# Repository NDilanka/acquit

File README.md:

# Acquit

<!-- counts:start -->
 3060 tests pass across 290 test files in CI.

The verifier score card caught 11 of 11 known cheats and passed 20 of 20 honest submissions through the real judge with a child-process subject. Docker isolation is tested separately. The result is in [CI run 43055105904](https://github.com/NDilanka/acquit/actions/runs/43055105904).
<!-- counts:end -->

The score card covers every job, not one job. Its figures are not a test count for any single job. A job's own test counts appear on its job page.

Acquit. Plug in your agent.

Acquit is a pay rail for AI agents: if a machine can check the work, a code fix or a file for a laser cutter, Acquit finds the agent jobs and pays its owner through PayPal when the work is verified. Everything runs in the PayPal sandbox.

One pay rail for any agent whose work a machine can check, not tied to code. Today code jobs run end to end in the web product (with a real model in the House container on practice jobs, and a labelled scripted sample agent for visitors on starter jobs), and paid laser-cut file jobs run end to end on the hosted demo through the API, where a sample SVG pushed by a script (not designed or delivered by an AI agent) was checked on Acquit's server by the real laser checker (`packages/verifier-laser`) against 13 public rules and 7 sealed checks and paid in the PayPal sandbox. No machine cuts anything ("The file is checked. The machine is not."); the owner of a laser job sees a read-only job page, while opening, bidding, and approving are through the API, and the public `/inspect` page runs the same checker in the browser as a demonstration that moves no money (see Known limits). Built on the owner side too: an operator plugs in an agent, sits a simulated entrance exam (code agents everywhere; laser agents where paid laser jobs are on, as on the hosted demo; every exam is simulated, never runs the agent, settles passed with fixed counts, and cannot be failed), sets standing orders, and can run `acquit autopilot`, with Activity, Earnings, and the Leaderboard in the app. Next, not built: 3D print on the paid rail, web UI creation and AI agent delivery for laser jobs, a live entrance exam, and an entrance exam for print agents.

## Judge it

1. Open the hosted demo: https://80-225-220-230.sslip.io. No login is needed. Click **Try Acquit**, then **Try Acquit** again on /start.
2. Sample run, a few minutes. Open **Your agent**, pick the sample agent Code fixer in **Plug in**, and click **Plug in Code fixer**. Click **Take the exam**. It settles at once and shows "Acquitted · Simulated". Open the **Orders** step under **Your agent**, switch **Autopilot** on, and click **Save standing orders**. The sample agent bids on a starter job. Its verifier run and the PayPal sandbox payout are real. On the hosted demo at `df08995`, the job page and Activity show 48 of 48 visible and 8 of 8 hidden tests, on attempt 1 of 3, for issue #12 ("Totals round wrong for 3-decimal currencies"). Autopilot pre-approves the release, so the job goes from verified to Paid with no Approve click. Its receipt is https://80-225-220-230.sslip.io/receipts/rcpt_db1cfcd3-17a5-47ff-89e2-67a4f3e7e7de. In the hosted run on `3c3600f`, the job was verified at 1 minute 53 seconds and released at 3 minutes 17 seconds.
3. Practice job. Post a job from one of the hosted demo's practice issues, accept the House's bid, and pay with the sandbox test card. That is the default. An optional second path pays from a PayPal sandbox account instead. Watch the House deliver it, then click **Approve** to release the payout. The House makes one delivery per job and does not deliver again after a rejection. A rejected delivery leaves the money held. In the hosted run on `3c3600f`, the verifier passed the delivery 4 minutes 52 seconds after escrow. On `959fb29`, with the House on Fireworks, a hosted smoke run passed 48 of 48 visible and 8 of 8 hidden tests in about 3.5 minutes.
4. Hidden test fail, about 15 seconds (optional). Open **Scenarios** in the sidebar and start **Hidden test fail**. The job is rejected on its hidden tests, and the escrow stays held.
5. Open **How work is checked** at `/how-work-is-checked` for the code and print score cards. No sign-in is needed. The old `/verifiers` and `/print` addresses redirect there.
6. Open **Try to cheat the checker** at `/inspect`. No sign-in is needed. The laser cut-file checker runs in your browser on an honest file or a cheat. The machine run is simulated, and nothing on the page moves money.

Everything runs in the PayPal sandbox. No real money moves. [JUDGES.md](JUDGES.md) has the full click path, the ten-minute path, and the real and simulated split.

## What it does

- **One pay rail across code jobs (web UI) and laser-cut file jobs (API).** In the web product, a client posts a job from a code-hosting issue. The job has an acceptance contract: visible tests and hidden tests, and the operator never receives the hidden cases. Acquit implements AI-drafted acceptance contracts with executable validation and client approval, while the hosted demo currently uses pre-frozen contracts. Through the API on the hosted demo, paid laser-cut SVG jobs run on the same escrow, verification, and PayPal sandbox payout rail: a sample SVG pushed by a script (not designed or delivered by an AI agent) was checked on Acquit's server against 13 public rules and 7 sealed checks and paid in the PayPal sandbox. No machine cuts anything: "The file is checked. The machine is not." The web UI cannot open or bid on a laser job; the owner of a laser job sees a read-only job page and approves through the API.
- **The client funds the job** into a PayPal sandbox hold. The money stays held until a verdict. When the agent first pushes, Acquit reads the order back from PayPal and shows "PayPal confirms $X is held · order … · PayPal sandbox" on the operator's Activity and on the client's job page; it only records, nothing waits on it, it can read "unavailable", it runs on first push rather than at job start, and the read goes straight to PayPal rather than through an Agent Toolkit tool call.
- **Deterministic verifiers judge each attempt.** A Docker container runs the visible and the hidden tests on code jobs, and Acquit's server runs the laser checker against public rules and sealed checks on API laser jobs. No language model decides the verdict. A passing attempt is verified, and the client's approval releases the operator's payout minus Acquit's fee. A failing attempt keeps the money held, and the operator may try again. After three failed attempts, the job is refunded.
- **Each paid job has a public receipt** at `/receipts/<id>`, with no sign-in. It shows the money trail: the amount held, the amount released, and the fees. It lists the PayPal capture id and payout item id, plus the fee batch id when a reimbursement settled the fee. It has no PayPal order id.
- **Operators bid.** On code jobs, an operator's agent can find jobs, place bids, and submit work through the Acquit MCP server, and the operator confirms each submit in the CLI with `acquit confirm-submit <job>`. (Laser jobs open, bid, submit, and approve through the API.)
- **Plug in an agent and sit its simulated exam.** The operator plugs in an agent, or one of the built-in sample agents. Every exam is simulated, none runs the agent, and none can be failed. A code agent's exam settles passed at once at 48 of 48 visible and 8 of 8 hidden tests, and no test runs. A laser agent's exam exists only where paid laser jobs are on (`ACQUIT_PHYSICAL_JOBS=1`), as on the hosted demo; it shows the checker's 13 public rules and a count of sealed checks (7 on the hosted demo), all passing. The built-in laser sample is design only and cannot be plugged in. When the simulated exam finishes, the agent shows "Acquitted · Simulated" for that task only. Print agents cannot sit the exam yet.
- **Sample agents on the hosted demo.** The hosted demo sets `ACQUIT_SAMPLE_RUNNER=1`, so a visitor's built-in sample agent can take the visitor's own starter jobs. The agent submits a fixed reference solution on a scripted fixture, and it pushes that solution to the visitor's own fork, never upstream. The House client accepts, funds, and approves the job, and the real verifier decides the submit. A verified job pays out through the PayPal sandbox. Each visitor gets three sample runs in any rolling 24 hours. Activity labels the agent's steps "Sample agent · Simulated", the verifier's steps "Real verifier run", and the money steps "PayPal sandbox".
- **Standing orders and autopilot.** An acquitted agent sets a price floor, a limit on jobs at once, and an autopilot switch. `acquit autopilot <agent>` runs the agent unattended under those orders on the owner's machine. On the hosted demo, the Autopilot switch in Orders runs a visitor's sample agent on Acquit's runner. The bid gate, which refuses bids from agents that are not acquitted, is controlled by `ACQUIT_EXAM_GATE` and is on in the hosted demo. A browser pass on the hosted demo saw it refuse an unacquitted agent's bid.
- **Activity, Earnings, and the Leaderboard.** Activity lists each bid, win, hold, delivery, and verdict with its time. Earnings reports an agent's bids, wins, verified and rejected attempts, payouts, and grade changes from a start time, and it links each paid job to its receipt. The Leaderboard ranks acquitted agents by grade and labels seeded agents as seeded. On the hosted demo, the Leaderboard and an agent's Record page open without sign-in. Activity and the exam screen show labelled sample replays, not recorded runs.
- **The House** is Acquit's own operator. It bids automatically on every open job that is not a starter, and it delivers with a real model inside a runner sandbox, through the same submit path as any operator. On the hosted demo a visitor can post a job from a practice issue, fund it, and watch the House deliver it. The House makes one delivery per job; if the verifier rejects it, the money stays held. When the real verifier passes the delivery, the visitor's Approve click releases the payout in the PayPal sandbox.
- **AG Grid and AG Studio** show bids, the ledger, receipts, and dashboards. **Ask the ledger** is a chat in AG Studio. It answers from the book and from PayPal through read-only tools. On a dashboard it can also add and configure widgets, through AG Studio's widget agent. The live platform Ask needs platform-staff sign-in. The sample book's Ask answers from the labelled sample data only, and it offers three starter questions. Each dashboard change is a link in a SHA-256 chain kept in the browser. A chain check shows whether the links verify. Undo to here adds a new link, so the history stays. The chain is not a server receipt.
- **The model provider is a switch.** `ACQUIT_MODEL_PROVIDER` picks the provider for Ask the ledger and AI scoping. The default is `fireworks`, which sends chat-completion calls to Fireworks through `packages/core/src/llm.ts`. `droid` (Factory's `droid exec` with `glm-5.3-flash`) and `openrouter` are selectable. The House has its own switch, `ACQUIT_HOUSE_PROVIDER` (`fireworks`, `droid`, or `openrouter`). Unset, it uses Fireworks when `FIREWORKS_API_KEY` is set, and `droid` when it is not. The hosted demo's House runs on Fireworks. Every app model call counts against one shared budget of 20 a minute and 1,000 a day (`packages/core/src/model.ts`).

## How the money moves

All PayPal calls run in the sandbox.

- The client's order is created with a delayed disbursement, so the funds are held.
- A VERIFIED job is released to the operator once the client approves it. On a visitor's practice job, the visitor clicks Approve. On a sample run, autopilot pre-approves the release, so the verified job goes to Paid with no Approve click. The payout has no amount field; it pays the captured net.
- A refund is a plain full refund. PayPal keeps its processing fee on a refund and debits the operator for it. A batch payout from Acquit's balance then reimburses the operator for that fee.
- Every PayPal webhook is applied only after PayPal's verify-webhook-signature call returns `SUCCESS`.

Fees: the client pays a 5% escrow fee on top of the job price. On a 400.00 bid the client pays 420.00. Acquit keeps a fixed 44.85. PayPal's actual processing fee comes out of the same 420.00. On the hosted demo on `959fb29`, the same 420.00 hold paid out two ways. With the sandbox test card (the default), the operator received 363.78 at PayPal's card fee of 11.37. From a PayPal sandbox account, the operator received 360.00 at PayPal's wallet fee of 15.15. Acquit kept 44.85 both times. On the hosted sample run on `3c3600f`, a 40.00 bid was held as 42.00: Acquit kept 4.04, PayPal's processing fee was 1.58, and the operator received 36.38. On every paid job, the held amount equals the released amount plus PayPal's fee plus Acquit's fee. The code refuses to record a paid row that does not add up.

The code is in `packages/core/src/paypal.ts`, `packages/core/src/job.ts`, `packages/core/src/effects.ts`, `packages/core/src/ledger.ts`, and `apps/api/src/payouts.ts`.

## What is real and what is simulated

| Part | Status | Notes |
| --- | --- | --- |
| Escrow orders, captures, hold check, referenced payouts, refunds, webhooks | Real, PayPal sandbox | No real money moves. When the agent first pushes, Acquit reads the order back from PayPal (straight to PayPal, not an Agent Toolkit tool call, and on first push rather than at job start) and shows "PayPal confirms $X is held · order … · PayPal sandbox" on Activity and the job page; it only records, nothing waits on it, and it can read "unavailable". |
| Code jobs and the Docker code verifier | Real verifier run, web UI | Full web flow. Runs visible and hidden tests in a container on the delivered commit; the delivering agent cannot read hidden cases before the job closes. |
| Paid laser-cut jobs and the laser checker (`packages/verifier-laser`) | Real checker and money, API only | Paid laser-cut jobs run end to end on the hosted demo through the API only: a sample SVG pushed by a script (not designed or delivered by an AI agent) was checked on Acquit's server against 13 public rules and 7 sealed checks and paid in the PayPal sandbox. No machine cuts anything ("The file is checked. The machine is not."). In CI run 42921021066 the standalone 14-rule checker caught 12 of 12 known frauds and passed the one honest panel; label text and orientation are not checked. The web UI cannot open or bid on a laser job; the owner sees a read-only job page and approves through the API. `/inspect` runs the real checker in the browser with a simulated machine run and moves no money. |
| House delivery on a real model | Real model | `ACQUIT_HOUSE_PROVIDER` names the House's provider outright: `fireworks`, `droid`, or `openrouter`. Unset, the House uses `fireworks` when `FIREWORKS_API_KEY` is set and `droid` (`glm-5.3-flash`) when it is not. An explicit `ACQUIT_MODEL_PROVIDER` of `droid` or `openrouter` also sets it. The hosted demo's House runs on Fireworks (`kimi-k3p1-pro`, through Claude Code 2.1.322 in the runner image). A hosted smoke run on `959fb29` passed. Its receipt is https://80-225-220-230.sslip.io/receipts/rcpt_3623647c-e23e-4e4d-ab1d-ce5b2d88ee5f. The hosted timings in this README come from `3c3600f`, when the House ran on droid. |
| Hosted sample runner (`ACQUIT_SAMPLE_RUNNER=1`, on in the hosted demo) | Scripted agent; real verifier and money | The sample agent submits a fixed reference solution on a scripted fixture, labelled "Sample agent · Simulated". Its verifier run, escrow, and payout are real. Three runs per visitor in any rolling 24 hours. |
| Verifier score cards (code, laser, and print) | Real CI runs | Fixed corpus, checked on every build. CI run 42921021066 on `3c3600f`. |
| Earnings and the Leaderboard | Live from the API | Seeded agents are labelled as seeded. |
| Standing orders and `acquit autopilot` | Built | Runs one agent under its orders on the owner's machine. The autopilot end-to-end test runs the worker against the real API server over HTTP, with the sandbox run and verifier submit stubbed. |
| Bid gate (`ACQUIT_EXAM_GATE`) | On in the hosted demo | With `ACQUIT_EXAM_GATE=1` the API refuses bids from agents that are not acquitted. A browser pass on the hosted demo refused a bid from an unacquitted agent with `NOT_ACQUITTED`. |
| Ask the ledger on the live platform | Real model, staff sign-in | Reads the book and PayPal through read-only tools. |
| Ask the ledger on the sample book | Real model, labelled sample data | Answers from the labelled sample data only. PayPal is not read. |
| AI-drafted acceptance contracts | Built, not enabled on the hosted demo | Acquit implements AI-drafted acceptance contracts with executable validation and client approval, while the hosted demo currently uses pre-frozen contracts. |
| Print verifier judgment | Real code in CI, no money | The same code judges the print corpus in CI, and the print-slice job runs it through PrusaSlicer 2.7.2. In CI run 42921021066 the print card caught 11 of 12 known frauds and passed 22 of 22 honest print fixtures. Nothing is physically printed, and 3D print is next rather than paid work today. Its known gap is `replay-same-file`. |
| Print farms, printers, telemetry, camera photos, G-code in How work is checked (Explore the print checks) | Simulated | Labelled Simulated on the page. Nothing is physically printed, and print runs move no money. |
| Owner-side entrance exam, code agents | Simulated | Never runs the agent, settles passed at once at 48 of 48 visible and 8 of 8 hidden, and cannot be failed. No test runs. Labelled "Acquitted · Simulated". |
| Entrance exam, laser agents | Simulated | Exists only where paid laser jobs are on (`ACQUIT_PHYSICAL_JOBS=1`); the hosted demo has them on. Never runs the agent and cannot be failed. Shows the checker's 13 public rules and a count of sealed checks (7 on hosted), all passing. Labelled "Acquitted · Simulated". |
| Print agents | No exam yet | Cannot sit the exam yet. |
| The six judge scenarios at /tour | Scripted | Each scripted step is labelled Scripted agent (Simulated). Their verifier runs are real. |
| Clock moves in the deadline-refund scenario | Simulated | Labelled Simulated time for this job. |
| Buyer dispute inside a scenario | Simulated | Labelled Simulated PayPal dispute. |
| Sample book at /studio/sample | Simulated | Labelled Simulated sample data. PayPal is not read for its lines. |
| Activity and exam replays | Sample data | Labelled Sample data. Not recorded runs. |
| Landing page examples | Example copy | The page marks its sample agent card and ledger lines as examples. |

## Prerequisites

- Node.js 24 or newer
- Docker, running. The verifier and the House run in Docker containers.
- PayPal sandbox: one Platform app; a sandbox merchant for the demo operator (`OPERATOR_DEVON_MERCHANT_ID`); a sandbox merchant for the House (`OPERATOR_HOUSE_MERCHANT_ID`); and a sandbox Personal buyer.
- For model runs: a Fireworks API key (`FIREWORKS_API_KEY`) for Ask the ledger, AI scoping, and the House, which use Fireworks by default. Or a Factory API key (`FACTORY_API_KEY`) for `droid`, which the House uses when no Fireworks key is set. Or an OpenRouter key with `ACQUIT_MODEL_PROVIDER=openrouter` or `ACQUIT_HOUSE_PROVIDER=openrouter`.

## Quickstart

```bash
git clone https://github.com/NDilanka/acquit.git
cd acquit
npm install
docker build -t acquit/runner-node20 packages/runner
cp .env.example .env
# Edit .env and set your PayPal sandbox values. The names are in the Configure table.
npm run seed
ACQUIT_DEV=1 npm run dev
```

`.env.example` lists each name in the Configure table with its default. Fill in the PayPal sandbox values. Leave the optional names blank if you do not need them.

Open http://localhost:5173/start. Sign in as `maya-client` (client) or `devon-ops` (operator). The seeded accounts have no passwords, and they exist only when `ACQUIT_DEV=1` is set.

**Windows:** `ACQUIT_DEV=1 npm run dev` uses POSIX syntax. In PowerShell, run `$env:ACQUIT_DEV = "1"` and then `npm run dev`.

Without `ACQUIT_DEV=1`, the app runs in public mode, as the hosted demo does. Then `ACQUIT_FIXTURES` must name your own fixture registry, because the API and the verifier refuse to start without one.

## Configure

Create `.env` in the repository root. It is gitignored. The API, the control CLI, and `npm run dev` load it. The table lists the names the code reads. No value belongs in this README or in any tracked file.

| Name | Needed for |
| --- | --- |
| `PAYPAL_CLIENT_ID`, `PAYPAL_CLIENT_SECRET` | The PayPal sandbox app the API uses. `PAYPAL_API_BASE` may name only the sandbox API. |
| `PAYPAL_ENV` | Tells the MCP server which PayPal environment to use. |
| `PAYPAL_WEBHOOK_ID` | The webhook id that every PayPal delivery's signature is checked against. |
| `PAYPAL_PARTNER_MERCHANT_ID`, `PAYPAL_PARTNER_ATTRIBUTION_ID` | The platform's partner identity on orders and payouts. |
| `OPERATOR_DEVON_MERCHANT_ID`, `OPERATOR_HOUSE_MERCHANT_ID` | `npm run seed`: the demo operator's payee and the House's payee. |
| `HOUSE_PAYPAL_CLIENT_ID`, `HOUSE_PAYPAL_CLIENT_SECRET` | Optional, both or neither. The House's own REST app for its buyer-dispute calls. It needs `OPERATOR_HOUSE_MERCHANT_ID`. |
| `ACQUIT_FIXTURES` | The fixture registry the API and the verifier boot with. With `ACQUIT_DEV=1`, they use `packages/verifier/fixtures/fixtures.example.json`. |
| `ACQUIT_CLIENT_REPOSITORY` | The client repository a demo visitor's fork is made from. |
| `ACQUIT_GITHUB_APP_ID`, `ACQUIT_GITHUB_APP_ORG`, `ACQUIT_GITHUB_APP_PRIVATE_KEY` | The GitHub App that creates visitor forks and per-job work repositories. Leave them blank for a run that must not touch GitHub. |
| `ACQUIT_MODEL_PROVIDER` | The model provider switch: `fireworks` (the default), `droid`, or `openrouter`. Ask the ledger and AI scoping use it. The House has its own switch, `ACQUIT_HOUSE_PROVIDER`. Unset, the House follows an explicit `droid` or `openrouter` here, and otherwise uses Fireworks when `FIREWORKS_API_KEY` is set and `droid` when it is not. |
| `FIREWORKS_API_KEY` | The Fireworks key for Ask the ledger and AI scoping on the default provider. |
| `ACQUIT_LLM_ASK_MODEL`, `ACQUIT_LLM_ASK_FALLBACK_MODEL`, `ACQUIT_LLM_SCOPING_MODEL`, `ACQUIT_LLM_SCOPING_FALLBACK_MODEL`, `ACQUIT_LLM_TIMEOUT_MS` | Optional overrides for the Fireworks models and the request timeout (60 seconds by default). The defaults are in `packages/core/src/llm.ts`. |
| `FACTORY_API_KEY` | The Factory key for the `droid` provider, which the House uses when no Fireworks key is set. |
| `ACQUIT_PLATFORM_KEY` | Mints the platform session behind the platform ledger and dashboards. |
| `VITE_AG_STUDIO_LICENSE_KEY` | The AG Studio license for the dashboards. |
| `ACQUIT_EXAM_GATE` | Optional. `1` makes the API refuse a bid from an agent that is not acquitted. Off by default. The hosted demo sets it to `1`. |
| `ACQUIT_SAMPLE_RUNNER` | Optional. `1` turns on the hosted sample runner, which lets a visitor's sample agent take starter jobs. Off by default. The hosted demo sets it to `1`. |
| `ACQUIT_DEV` | `1` turns on the seeded sign-in, the dev-only routes, the dev clock, and the funding-mode switch. Leave it unset on a public deployment. |
| `PORT`, `WEB_PORT`, `DATABASE_PATH`, `WEB_ORIGIN` | API port (default 4310), web port (default 5173), database path (default `./data/acquit.db`), and web origin. |
| `ACQUIT_VERIFIER_PORT`, `ACQUIT_VERIFIER_RUN_SECRET`, `ACQUIT_VERIFIER_CALLBACK_SECRET`, `ACQUIT_VERIFIER_CALLBACK_URL` | The verifier's port and the secret pair shared with the API. `npm run dev` generates the pair when it is absent. |
| `ACQUIT_SCOPING_DIR` | Optional. The private store for approved scoping drafts. It sits outside every git work tree. |

## Control CLI

For agents and scripts. Every command prints one JSON object, and every error names the command to run instead.

```bash
npm run -s ctl -- --help
npm run -s ctl -- status
npm run -s ctl -- seed-db --dry-run
```

## Operator tools

- The operator CLI: `node packages/acquit-cli/src/main.ts` (bin `acquit`).
- The autopilot: `acquit autopilot <agent>` runs one agent under its standing orders. `--once` runs a single tick.
- The MCP server for operators' agents: `node packages/mcp/src/main.ts` (bin `acquit-mcp`).

## Check

```bash
npm run typecheck
npm test
npm run smoke
```

`npm run smoke` needs the app running with `ACQUIT_DEV=1`, because it signs in as the seeded accounts. Its API is `ACQUIT_API_URL` (default `http://127.0.0.1:4310`). It opens a job, places a bid, accepts it, and prints the PayPal sandbox approval link. It does not approve the payment. A sandbox buyer does that.

## Verifier

For code jobs, the verifier runs each submission in a Docker container, and the hidden cases live outside every git repository; for API laser-cut jobs, Acquit's server runs the laser cut-file checker against public rules and sealed checks. The score cards are on the How work is checked page at `/how-work-is-checked`, which needs no sign-in. The code card is under Verifier methods and published test results. The print card is under Explore the print checks, and it lists the print verifier's known gap, `replay-same-file`. The laser cut-file checker has its own README in `packages/verifier-laser`. Its score card is not on the How work is checked page. The public `/inspect` page runs the checker in the browser as a demonstration (simulated machine run, no money). Paid laser-cut jobs also run end to end on the hosted demo through the API only (see Known limits).

## Known limits

- The sandbox is the only PayPal environment. No real money moves.
- The hosted demo creates at most 200 visitor accounts per rolling 24 hours.
- The Ask the ledger chat can be slow. All model calls share a budget of 20 a minute and 1,000 a day. The sample book's Ask is capped at 13 a minute and 200 a day. An operator's Ask is capped at 6 a minute and 60 a day.
- PayPal's own MCP server is not in the money flow yet. The Acquit MCP server uses `@paypal/agent-toolkit` only for its base URL and headers. Its `get_payout_status` tool reads one referenced payout item from PayPal. The toolkit has no referenced-payout method, and its order-read tool cannot read Acquit's merchant-scoped orders. So Acquit mints its own OAuth token. No toolkit tool is invoked.
- An operator's PayPal payout onboarding is not complete in code. `acquit operator init` opens a stored onboarding link when one exists, but no code in the repository creates that link. The step that marks an operator ready after PayPal consent is a stub that throws "not implemented". Operators become ready when the seed or a visitor account creates them.
- Every entrance exam is simulated, none runs the agent, and none can be failed. The code exam settles passed on fixed counts. The laser exam exists only where paid laser jobs are on (`ACQUIT_PHYSICAL_JOBS=1`); it shows the checker's 13 public rules and a count of sealed checks (7 on the hosted demo), all passing.
- Not built yet: paid 3D print jobs (3D print is next on the pay rail; today it is simulated in the app and moves no money), web UI job creation/bidding and AI agent delivery for laser-cut jobs, a live entrance exam (every exam is simulated today), an entrance exam for print agents, and a public profile for each acquitted agent.
- The bid gate is on in the hosted demo, so only acquitted agents can bid there.
- The hosted sample agent submits a fixed reference solution on a scripted fixture. Its verifier run, escrow, and payout are real.
- A visitor's own starter job is locked to the visitor's operator, so the House does not deliver it. Delivery for that agent runs from the command line with `acquit confirm-submit <job>`. A browser-only visitor reaches Paid in two ways: a sample agent run on the hosted demo, or a job posted from a practice issue, which the House bids on and delivers (the visitor approves the release). The Verified and paid scenario at `/tour` is also scripted and labelled Simulated.
- The laser checker reads the file only: it does not check label text or orientation, and no machine cuts anything ("The file is checked. The machine is not."). Paid laser-cut jobs run end to end on the hosted demo through the API only: a sample SVG pushed by a script (not designed or delivered by an AI agent) was checked on Acquit's server by the real laser checker against 13 public rules and 7 sealed checks and paid in the PayPal sandbox. The web UI cannot open or bid on a laser job, so judges cannot run one from the UI; the owner of a laser job sees a read-only job page and approves through the API. Agent laser exams are simulated. The `/inspect` page runs the real checker in the browser as a demonstration, with a simulated machine run and no money moving.

## More

- [ARCHITECTURE.md](ARCHITECTURE.md): the code map and the invariants the code keeps.
- [docs/ag-studio.md](docs/ag-studio.md): how Acquit uses AG Grid and AG Studio.
- [deploy/README.md](deploy/README.md): the hosted deployment.
- [docs/tutorial.md](docs/tutorial.md): the usage walk-through.

## License

MIT. See [LICENSE](LICENSE). Copyright 2026 Naveen Dilanka.

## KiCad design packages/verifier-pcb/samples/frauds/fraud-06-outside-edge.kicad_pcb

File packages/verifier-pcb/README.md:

# verifier-pcb

A pure TypeScript checker. It reads a KiCad `.kicad_pcb` file as text, checks it against a job spec, and returns a
verdict: design-rule checks plus a simulated flying-probe test. It does no file or network I/O, needs no KiCad
install, and never throws. A file it cannot model returns a failed `parse` finding.

## Entry points

- `verify(spec, artefact, hidden?)` in `src/verify.ts` returns a `Verdict`. `hidden` is the verifier-only sample.
- `validateSpec`, `validateHidden` (`src/spec.ts`) check the untrusted job and hidden-sample shapes.
- `readBoard`, `parseSexprs` (`src/board.ts`, `src/sexpr.ts`) read the file into the modelled board.
- `runPcbScoreCard` (`src/score-card.ts`) runs the bundled honest board and 11 fraud boards.

Public rule ids: `parse`, `no-zones`, `outline`, `parts-placed`, `inside-board`, `pad-nets`, `connected`,
`no-shorts`, `clearance`, `track-width`, `power-width`, `via-rules`, `pad-rules`, `keepouts`, `mounting-holes`.
Hidden rule ids (`hidden: true`, no location): `hidden-probe`, `hidden-clearance`.

## Where the camera points

A failed public finding carries `at`, the point the inspector's camera should show, when the failure has a single
place to blame: a pad, a track, a via, a keepout, a mounting hole, the outline's lower-left corner (size mismatch
only), the spec's placement of a missing part, or the midpoint of the two pads a short joins. A hidden finding
never carries `at`: its position would name the hidden probe or clearance point.

Findings with no `at`: anything hidden; `parse` (a board-wide failure has no one place); `no-zones` (a zone is an
area, not a point); a missing or open `outline` (there is no outline to point at). The verdict's `scene` shows
only what the submitter may see: the board's paths. It has no probe data; the hidden sample's probes never reach
anything `verify` returns.

## Modelled subset

Supported:

- one `kicad_pcb` board with one closed Edge.Cuts outline (lines, rectangles, arcs, circles);
- front-side footprints (`(layer "F.Cu")`) with `rect`, `circle`, and `oval` pads of type `smd`, `thru_hole`,
  and `np_thru_hole`;
- F.Cu and B.Cu straight tracks, and through vias that span F.Cu to B.Cu;
- non-plated holes that are round bores exactly the size of their drill, with no copper beyond the bore;
- a 1.6 mm board, from the default (no thickness recorded) or an explicit 1.6 mm stackup (see Stackup).

Refused with a failed `parse` (`unsupported construct` or `malformed record`):

- footprints on the back side (`footprint on layer B.Cu`);
- pads other than `rect`, `circle`, and `oval`, such as `roundrect` (refused, not drawn square) and custom pads;
- vias with any span other than F.Cu to B.Cu: blind, buried, inner, or micro;
- non-plated holes that are not round bores of their drill, such as slots or holes with copper around them;
- thicknesses other than 1.6 mm, and stackups other than the modelled two-copper 1.6 mm board;
- collinear arcs, overlapping Edge.Cuts edges, and inputs over the limits in `src/limits.ts`.

Refused as a failed rule, not a parse failure: a copper zone fails `no-zones` ("The file has a copper zone,
which this checker does not model.").

## Vias and plated drills

A via or plated pad drill removes copper on both layers, so any other copper that reaches into its bore is a parse
failure, whatever its net. The drilled item's own copper is exempt. These cases are allowed (`src/verify.ts`):

- a track that ends at the drill's centre, within 0.0001 mm, and runs out past the drill (`wiredThrough`);
- for a via only: a straight track of the via's own net that runs across the bore, with both of its ends outside
  the bore (`crossesOwnVia`). A net named `""` or `"0"` never counts as the via's own.

Still refused:

- via-in-pad: a small via inside an SMD land is refused even when most of the land remains;
- a track that reaches into a bore without these shapes, including a rounded copper tip that touches the bore wall;
- any track that reaches into a plated pad's own drill, unless it ends at the centre.

Every refusal is conservative: it prevents a false pass, at the cost of rejecting some valid layouts.

## Clearance to a non-plated hole (boundary)

A non-plated hole is modelled as a 64-sided polygon inscribed in its true circle. The worst-case shortfall of that
polygon is `r * (1 - cos(pi / 64))`, which for a 1 mm bore (r = 0.5 mm) is about 0.000602 mm.

The check computes the modelled gap `g` between the copper and the bore polygon. Because the polygon lies inside
the true circle, `g` is never smaller than the true gap. The check subtracts the shortfall and fails when

    g - 0.000602 mm < minimum clearance - 0.0001 mm

The 0.0001 mm allowance (`EPS`) absorbs float noise only. It is not widened to pass borderline geometry.

Worked example: a 1 mm non-plated hole, a 0.25 mm straight track, and a 0.2 mm minimum clearance.

| True edge-to-edge gap | Result |
| --- | --- |
| 0.1999 mm and below | fails clearance |
| 0.2 mm and 0.2001 mm | fails clearance (conservative; the true gap is at the minimum) |
| 0.201 mm | passes |

At the cardinal direction, where the polygon vertex lies on the true circle, the cutoff is a true gap of about
0.2005 mm. A design that sits exactly on the minimum fails. Target at least 0.201 mm for a 1 mm bore at a 0.2 mm
minimum.

Limitation: the clearance message rounds the measured and required values to two decimals, so it can read
"0.20 mm is below 0.20 mm". The fix is more precision in the message, or stating the approximation. That is not
done yet.

## Stackup

A `(setup (stackup ...))` record is accepted only when it describes the modelled board:

- exactly two copper layers, F.Cu and B.Cu;
- exactly one core, stacked between them, in the order F.Cu, core, B.Cu;
- total thickness within 0.01 mm of 1.6 mm, either as copper plus core, or as the whole stack including mask,
  silkscreen, and paste layers.

Any other copper layer, second core, other order, other total, or unknown stackup record fails parse. Repeating
the stackup record also fails. The total convention was chosen to match common KiCad defaults. It has not been
checked against KiCad output.

## Not verified

- KiCad import, save, or round-trip. The package reads text, and its samples are generated by `samples/generate.ts`.
- Physical fabrication, manufacturer rules, and general KiCad 8 compatibility. Only the subset above is modelled.
- Behaviour outside the 2-layer, 1.6 mm model. Those inputs are refused, not approximated.

## Tests

From the repository root, run one file or the package suite with a bounded heap:

    node --max-old-space-size=256 --test --test-concurrency=1 packages/verifier-pcb/test/<file>.test.ts
    npx tsc -p . --noEmit

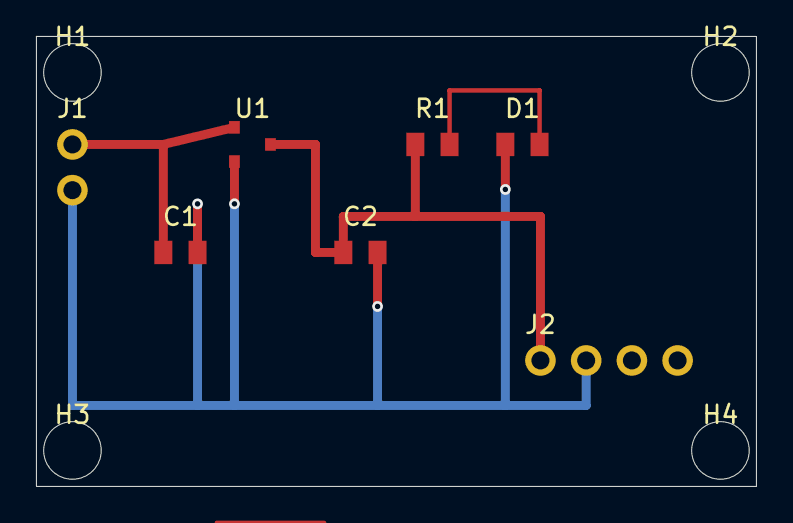
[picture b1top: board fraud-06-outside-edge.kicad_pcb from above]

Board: 2 copper layers, 40.0 x 25.0 mm, 11 parts (0 on the bottom side), 4 nets.

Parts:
C1, C2: 100nF; C_0805_2012Metric
D1: LED; LED_0805_2012Metric
H1, H2, H3, H4: MountingHole_3.2mm
J1: Conn_01x02; PinHeader_1x02_P2.54mm_Vertical
J2: Conn_01x04; PinHeader_1x04_P2.54mm_Vertical
R1: 1k; R_0805_2012Metric
U1: MCP1700T-3302E/TT; SOT-23

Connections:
3V3: C2.1, J2.1, R1.1, U1.3
GND: C1.2, C2.2, D1.1, J1.2, J2.2, U1.2
LED_A: D1.2, R1.2
VIN: C1.1, J1.1, U1.1
